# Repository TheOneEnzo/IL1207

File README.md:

# Smart Helmet PCB

Battery-powered smart helmet system with:
- ESP32
- GPS (SIM7600E)
- MPU-6050 IMU

## Features
- Modular design
- 3.3V regulated supply
- Motion detection

###
This PCB is meant to fit inside a helmet and detect when the helmet is struck or fast acceleration changes. It should then send a emergency message via the SIM7600E to a reciever with the position of the accident.

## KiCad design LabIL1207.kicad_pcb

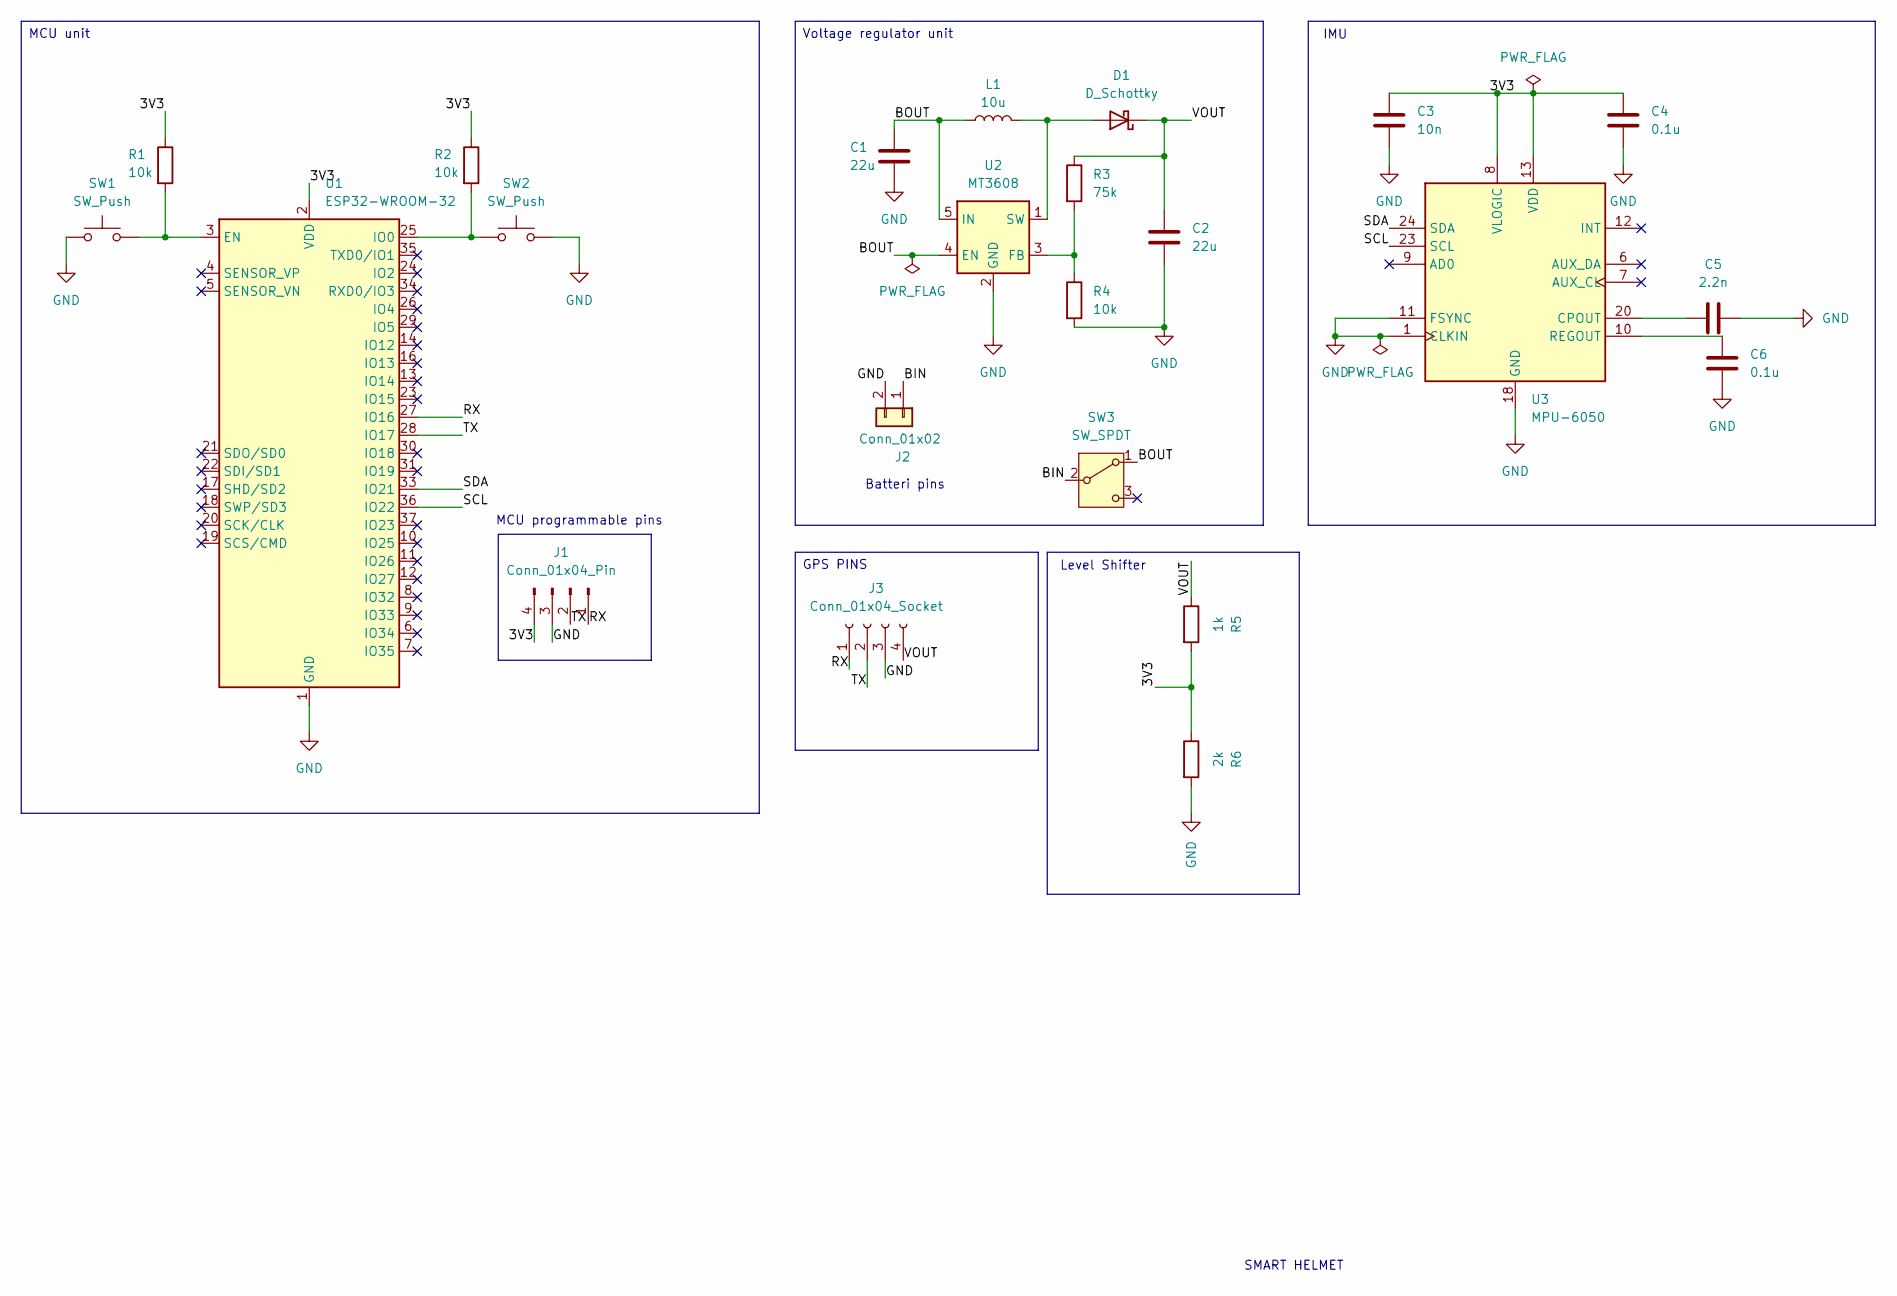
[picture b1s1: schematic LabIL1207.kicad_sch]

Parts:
C1, C2: 22u; C_0805_2012Metric_Pad1.18x1.45mm_HandSolder
C3: 10n; C_0603_1608Metric
C4, C6: 0.1u; C_0603_1608Metric
C5: 2.2n; C_0603_1608Metric
D1: D_Schottky; D_SMA_Handsoldering
J1: Conn_01x04_Pin; PinHeader_1x04_P2.54mm_Vertical
J2: Conn_01x02; PinHeader_1x02_P2.54mm_Vertical
J3: Conn_01x04_Socket; PinSocket_1x04_P2.54mm_Vertical
L1: 10u; L_Changjiang_FTC322510S
R1, R2, R4: 10k; R_0603_1608Metric
R3: 75k; R_0603_1608Metric
R5: 1k; R_0603_1608Metric
R6: 2k; R_0603_1608Metric
SW1, SW2: SW_Push; SW_PUSH_6mm
SW3: SW_SPDT; SW_E-Switch_EG1271_SPDT
U1: ESP32-WROOM-32
U2: MT3608; SOT-23-6
U3: MPU-6050; InvenSense_QFN-24_4x4mm_P0.5mm

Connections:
/3V3: C3.1, C4.1, J1.4, R1.1, R2.1, R5.2, R6.1, U1.2 (VDD), U3.8 (VLOGIC), U3.13 (VDD)
/BIN: J2.1, SW3.2 (B)
/BOUT: C1.1, L1.1, SW3.1 (A), U2.4 (EN), U2.5 (IN)
/RX: J1.1, J3.1, U1.27 (IO16)
/SCL: U1.36 (IO22), U3.23 (SCL)
/SDA: U1.33 (IO21), U3.24 (SDA)
/TX: J1.2, J3.2, U1.28 (IO17)
/VOUT: C2.1, D1.1 (K), J3.4, R3.1, R5.1
GND: C1.2, C2.2, C3.2, C4.2, C5.2, C6.2, J1.3, J2.2, J3.3, R4.2, R6.2, SW1.1, SW2.2, U1.1 (GND), U1.15 (GND), U1.38 (GND), U1.39 (GND), U2.2 (GND), U3.1 (CLKIN), U3.11 (FSYNC), U3.18 (GND)
unnamed: D1.2 (A), L1.2, U2.1 (SW)
unnamed: R1.2, SW1.2, U1.3 (EN)
unnamed: R2.2, SW2.1, U1.25 (IO0)
unnamed: R3.2, R4.1, U2.3 (FB)
unnamed: C5.1, U3.20 (CPOUT)
unnamed: C6.1, U3.10 (REGOUT)

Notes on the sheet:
Level Shifter
Batteri pins
SMART HELMET
IMU
MCU programmable pins
GPS PINS
Voltage regulator unit
MCU unit

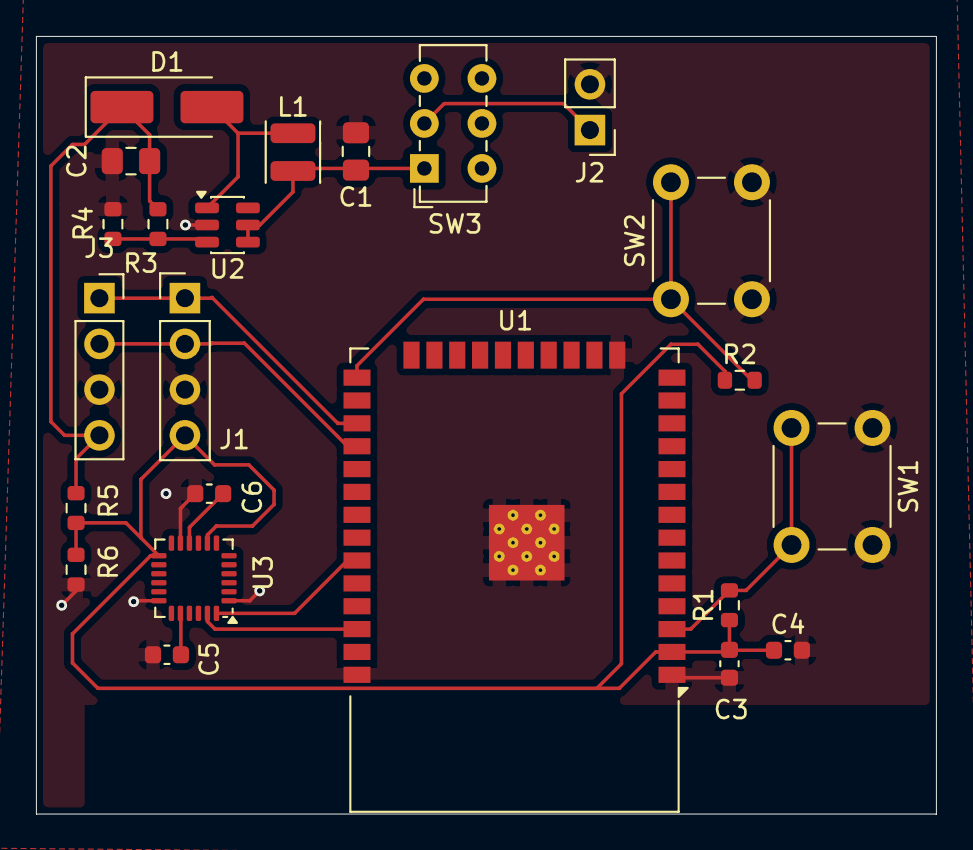
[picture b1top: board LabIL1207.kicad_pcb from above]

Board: 2 copper layers, 50.0 x 43.2 mm, 23 parts (0 on the bottom side), 15 nets.

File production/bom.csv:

Designator,Footprint,Quantity,Value,LCSC Part #
"C1, C2",0805,2,22u,
C3,0603,1,10n,
"C4, C6",0603,2,0.1u,
C5,0603,1,2.2n,
D1,D_SMA_Handsoldering,1,D_Schottky,
J1,PinHeader_1x04_P2.54mm_Vertical,1,Conn_01x04_Pin,
J2,PinHeader_1x02_P2.54mm_Vertical,1,Conn_01x02,
J3,PinSocket_1x04_P2.54mm_Vertical,1,Conn_01x04_Socket,
L1,L_Changjiang_FTC322510S,1,10u,
"R1, R2, R4",0603,3,10k,
R3,0603,1,75k,
R5,0603,1,1k,
R6,0603,1,2k,
"SW1, SW2",SW_PUSH_6mm,2,SW_Push,
SW3,SW_E-Switch_EG1271_SPDT,1,SW_SPDT,
U1,ESP32-WROOM-32,1,ESP32-WROOM-32,
U2,SOT-23-6,1,MT3608,
U3,InvenSense_QFN-24_4x4mm_P0.5mm,1,MPU-6050,

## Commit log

2026-04-17 git commit -m "Initial commit - Smart Helmet PCB design"
2026-04-17 Add initial README for Smart Helmet PCB project
2026-04-18 updated PCB design with better practices
2026-04-18 updated pcb
2026-04-18 Enhance README with PCB description and image
    Added a description of the PCB's purpose and functionality.
2026-04-20 Added level shifter
